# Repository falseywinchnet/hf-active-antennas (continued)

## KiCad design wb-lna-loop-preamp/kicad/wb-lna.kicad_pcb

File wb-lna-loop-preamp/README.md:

# WB-LNA: HF loop preamplifier

*Concept render: AI-generated (ChatGPT image generation) from the KiCad renders and the enclosure dimensions, with a ruler for scale. It shows the intended build; it is **not** a photograph of a built unit.*

WB-LNA is a single-ended HF (30 kHz – 30 MHz) low-noise amplifier with a high-impedance input. It suits a receiving loop or any other high-Z HF source.
- **Circuit:** 4× LSBF862 common source → 4× NSVF4009 common emitter with shunt-series feedback. The current is reused between the two stages.
- **Output:** a 3 dB π pad into 50 Ω SMA.
- **Power:** +12 V at 42 mA, from **either** the DC jack **or** phantom feed up the RF OUT coax.

## Performance
Simulated on the final board's layout-parasitic model, with a 50 Ω source and load at +12 V.

| | 1 MHz | 7 MHz | 14 MHz | 30 MHz |
|---|---|---|---|---|
| Gain | 24.0 dB | 24.0 dB | 24.0 dB | 23.2 dB |
| Noise figure | 0.80 dB | 0.81 dB | 0.87 dB | 1.14 dB |
| Noise temperature | 59 K | 60 K | 65 K | 87 K |
| Input return loss | 0.2 dB | 0.2 dB | 0.4 dB | 1.5 dB (high-Z input by design) |
| Output return loss | 52 dB | 46 dB | 37 dB | 24 dB |

**Linearity:**
- **Output P1dB:** +10.5 dBm (input −12.6 dBm).
- **OIP3 / IIP3** (−30 dBm/tone, 50 kHz spacing): +30.6 / +6.6 dBm at 7 MHz; +31.3 / +7.9 dBm at 28 MHz.
- **OIP2 / IIP2:** +36.3 / +12.3 dBm.
- **SFDR3 at 7 MHz:** 102 dB in 500 Hz.

**Low end:** flat to about 30 kHz; −3 dB at about 10 kHz.

**Stability:**
- **Tolerance corners:** 256 corners are all stable. They cover choke C and L, bead fits, trace and ground inductance, and gate-to-collector coupling.
- **Loop sources:** against any copper-wire loop into a receiver with |Γ| ≤ 1/3, the worst loop factor is 0.848.
- **Above 88 MHz:** μ ≥ 1.11 and μ′ ≥ 1.06.
- **Kicks:** node and differential kicks decay by ≥ 55 dB within 200 ns.

## How it works
- **Input:** the four LSBF862s run in parallel in common source.
  - Each has its own 100 nH‖60 Ω gate bead, with 100 kΩ gate bias and a BAV99 gate clamp.
  - The sources self-bias through R4/C4.
  - Paralleling four devices cuts en by about 2× against one device. Their combined input capacitance is the price; a loop's own reactance swamps it.
- **Drain:** loaded by 100 Ω AC, fed through a 1 mH choke.
- **Stage 2:** four onsemi NSVF4009 RF BJTs in common emitter.
  - R6/C8 provide shunt-series feedback and R7 the DC bias.
  - Each device has 22 Ω base and 10 Ω collector stoppers and 56 Ω emitter ballast.
- **Current reuse:** the JFET source bus is shared with the BJT collectors through L3, so the whole amplifier draws about 42 mA.
- **Output:** R8/C10 damp VHF, a 3 dB π pad (R40–R42) sets a clean 50 Ω match, and C13 blocks DC.
- **Protection:** a GDT (0.6 pF) plus 3× SP4022 on RF IN to the rear ground post, then VHF damping (L1‖R2).

**Power entry:** the two feeds are diode-ORed (D1/D8). The jack can never put DC on the receiver input, and the coax feed never appears on the jack.
- **Jack:** through a Würth 744222 common-mode choke. Its sleeve reaches board ground only through the choke winding.
- **Coax phantom feed:** L14 100 µH with 1 kΩ across it → L8 1 mH → a bead → 1 µF.
  - The 1 kΩ across L14 kills a series resonance between the two chokes. Without it, S22 has a −10 dB dip near 4 MHz.
- **Shared chain after the OR:** a PTC, a 15 V TVS, a 100 µH / 1 µF LC, then 22 Ω / 220 µF.
- **Differential rejection:** RF on the 12 V lead is rejected by ≥ 101 dB at 0.5–30 MHz, referred to the RF input.
- **Bias-T:** not supplied. Any bias-T rated ≥ 12 V / 100 mA with ≥ 1 kΩ choke impedance across 0.5–30 MHz will do.

## Plots

| plot | what |
|---|---|
| [`1_sparams_stability.png`](plots/1_sparams_stability.png) | S-parameters and μ/μ′ to 3 GHz |
| [`2_hf_gain_nf_match.png`](plots/2_hf_gain_nf_match.png) | HF gain, NF and match |
| [`3_transient_7MHz.png`](plots/3_transient_7MHz.png) | 7 MHz compression and collector swing |
| [`4_feedback_oscillation.png`](plots/4_feedback_oscillation.png) | output→input coupling test: ≤ 3.3 pF is stable, ≥ 10 pF oscillates |
| [`5_longrun_60s.png`](plots/5_longrun_60s.png) | 60 s runs, including power-up from the jack and from the coax |
| [`6_gain_nf_final.png`](plots/6_gain_nf_final.png) | gain and NF, final board |
| [`7_power_entry_chokes.png`](plots/7_power_entry_chokes.png) | power entry and choke impedances |

Plots 1–3, 6 and 7 use the layout-parasitic model. Plots 4 and 5 use the schematic without layout parasitics, because the layout model is too stiff for the long transients.

## LTspice model

`ltspice/wb-lna.asc` is the hand-laid schematic of the final circuit, with every board part. Keep `lsbf862-ltspice.lib`, `nsvf4009sg4-ltspice.lib` and `lna-parts.lib` next to it.
- **Test fixture:** V1 (AC 2) behind RS 50 Ω into RL 50 Ω, so `V(OUT)` is the transducer gain directly. The fixture is for simulation only.
- **Default analysis:** `.noise V(OUT) V1`, which reports NF re 50 Ω. Swap it for `.ac` to get gain.
- **Model fidelity:** checked against the design's reference netlist, it gives identical NF and gain within 0.1 dB.
- **Board copper:** the schematic carries no layout parasitics. The board's parasitic model, which the plots use, adds them.

## Board and ordering

**Board:**
- 92.4 × 42.4 mm, 2 layers, 1.6 mm FR-4, 1 oz copper, solid GND pours on both layers.
- **Enclosure:** Hammond 1591A (= RS PRO 153-3681, 100 × 50 × 25 mm).
- **Mounting:** 4 × M3 holes at 86.2 × 36.2 mm centres.
- **Connectors:** SMA RF IN on the front edge; SMA RF OUT and the 12 V jack on the rear edge.

**JLCPCB fabrication:** upload `jlcpcb/wb-lna_gerbers_drill.zip`.
- 2 layers, 1.6 mm, 1 oz;
- min track/clearance 0.2 mm, smallest via 0.6 / 0.3 mm.

**JLCPCB assembly:** `jlcpcb/BOM_JLCPCB.csv` and `jlcpcb/CPL_JLCPCB.csv`, on the same origin as the gerbers.
- **LCSC numbers:** left blank. Let JLC match parts by MPN or spec.
- **LSBF862:** buy from Linear Integrated Systems.
- **Candidate parts:** rows marked `candidate - verify before ordering` were not checked against a datasheet. They are the Murata beads L4/L5/L9/L10–L13, the R9 PTC and the C1 electrolytic.
- **Hand-solder:** the edge-mount SMAs X1/X2 and the THT jack X3.
- **Rotation:** check every part's rotation in the placement preview. This matters most for SOT-23, the SMA/SMB diodes, the electrolytic and the WE-SL2 choke; pin 1 of the choke is the dotted corner.

**Lands:**
- **J1–J4:** a custom SOT-23 land with shortened inner heels, so the source bus can run under the bodies.
- **Q1–Q4:** onsemi's SC-82FL land.
- **The 2220 chokes:** the B82442T datasheet pattern.

**Install:** the coax shield still carries common-mode RF. Fit a clip-on 31-mix ferrite on the coax at the amplifier.

## Files

| path | what |
|---|---|
| `ltspice/` | `wb-lna.asc` and its three model libraries |
| `images/` | concept render in the enclosure (AI-generated); 3D renders (iso, top), top copper coloured by net, schematic (PNG, SVG) |
| `plots/` | LTspice results (table above) |
| `jlcpcb/` | the gerber + drill zip (Protel extensions, Excellon mm, PTH/NPTH separate, job file), the unzipped files, `BOM_JLCPCB.csv`, `CPL_JLCPCB.csv` |
| `BOM.csv` | the full BOM: qty, designators, value, description, manufacturer, MPN, footprint, status |
| `kicad/` | `wb-lna.kicad_pcb`, the project, the custom footprint library `wblna.pretty`, the DRC report |
| `wb-lna.step` | 3D board model. The L6 body is a scaled stand-in. |

**Not claimed:** any surge/ESD rating or measured performance. All figures are simulation.

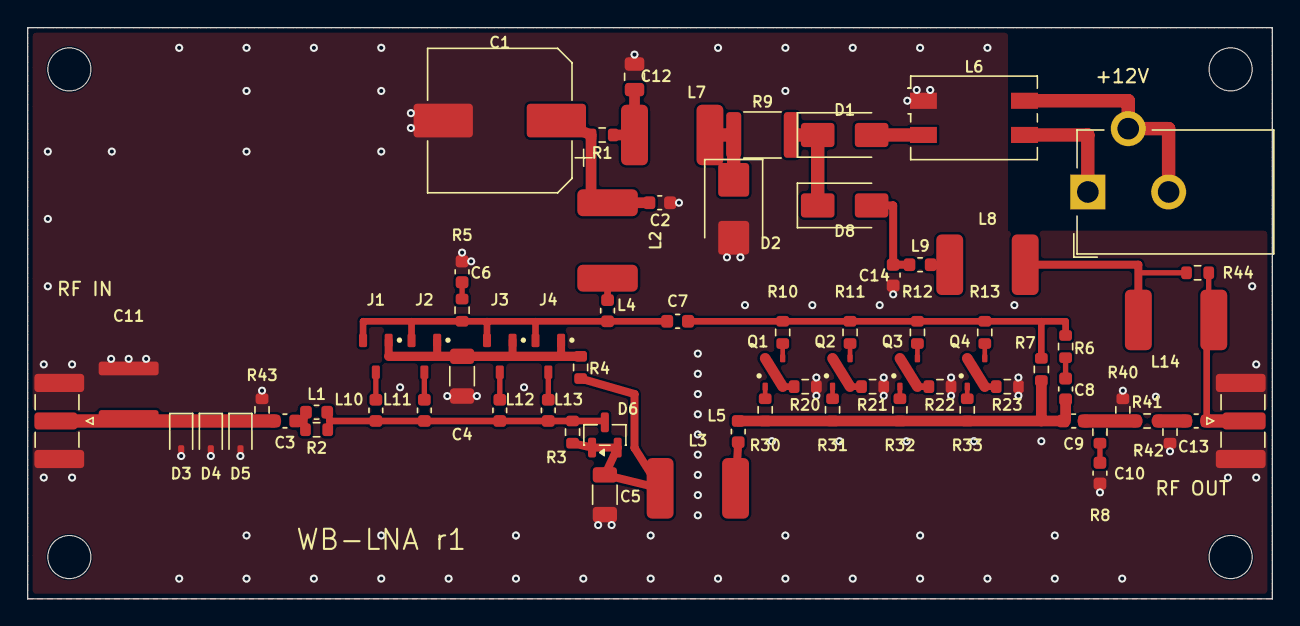
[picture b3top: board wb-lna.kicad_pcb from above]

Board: 2 copper layers, 92.4 x 42.4 mm, 76 parts (0 on the bottom side), 43 nets.

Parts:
C1: 220u; CP_Elec_10x10.5
C2: C2; C_0603_1608Metric
C3: C3; C_0603_1608Metric
C4: C4; C_1206_3216Metric
C5: C5; C_1206_3216Metric
C6: C6; C_0603_1608Metric
C7: C7; C_0603_1608Metric
C8: C8; C_0603_1608Metric
C9: C9; C_0603_1608Metric
C10: C10; C_0603_1608Metric
C11: GDT25-09-S1; GDT25_S1
C12: 1u; C_0805_2012Metric
C13, C14: 1u; C_0603_1608Metric
D1, D8: SS14; D_SMA
D2: SMBJ15A; D_SMB
D3, D4, D5: SP4022; D_SOD-323
D6: BAV99; SOT-23
H1, H2, H3, H4: M3; MountingHole_3.2mm_M3
J1, J2, J3, J4: LSBF862; SOT-23_WB
L1: 82nH; L_0603_1608Metric
L2, L3, L8: 1mH; L_2220_SIMID
L4, L5, L9: 600R@100M; L_0603_1608Metric
L6: 744222; L_CommonMode_Wuerth_WE-SL2
L7, L14: 100uH; L_2220_SIMID
L10, L11, L12, L13: bead; L_0603_1608Metric
Q1, Q2, Q3, Q4: NSVF4009SG4; SC-82FL_MCPH4
R1: R1; R_0603_1608Metric
R2: 47; R_0603_1608Metric
R3: R3; R_0603_1608Metric
R4: R4; R_0603_1608Metric
R5: R5; R_0603_1608Metric
R6: R6; R_0603_1608Metric
R7: R7; R_0603_1608Metric
R8: R8; R_0603_1608Metric
R9: PTC; R_1812_4532Metric
R10: R10; R_0603_1608Metric
R11: R11; R_0603_1608Metric
R12: R12; R_0603_1608Metric
R13: R13; R_0603_1608Metric
R20: R20; R_0603_1608Metric
R21: R21; R_0603_1608Metric
R22: R22; R_0603_1608Metric
R23: R23; R_0603_1608Metric
R30: R30; R_0603_1608Metric
R31: R31; R_0603_1608Metric
R32: R32; R_0603_1608Metric
R33: R33; R_0603_1608Metric
R40, R42: 294; R_0603_1608Metric
R41: 17.8; R_0603_1608Metric
R43: 4.7k; R_0603_1608Metric
R44: 1k; R_0603_1608Metric
X1: SMA RF IN; SMA_Samtec_SMA-J-P-H-ST-EM1_EdgeMount
X2: SMA RF OUT; SMA_Samtec_SMA-J-P-H-ST-EM1_EdgeMount
X3: 12V; BarrelJack_CUI_PJ-102AH_Horizontal

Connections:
B0: Q1.3, R10.2
B1: Q2.3, R11.2
B2: Q3.3, R12.2
B3: Q4.3, R13.2
BASE: C7.2, R6.2, R7.2, R10.1, R11.1, R12.1, R13.1
C0: Q1.1, R30.1
C1: Q2.1, R31.1
C2: Q3.1, R32.1
C3: Q4.1, R33.1
CBL_GND: L6.4, X3.2, X3.3
COLL: C8.1, C9.1, L5.2, R7.1, R30.2, R31.2, R32.2, R33.2
DQ: C6.1, R5.2
E0: Q1.2, Q1.4, R20.1
E1: Q2.2, Q2.4, R21.1
E2: Q3.2, Q3.4, R22.1
E3: Q4.2, Q4.4, R23.1
FB2: C8.2, R6.1
G0: J1.3, L10.2
G1: J2.3, L11.2
G2: J3.3, L12.2
G3: J4.3, L13.2
GATE: D6.3, L1.2, L10.1, L11.1, L12.1, L13.1, R2.2, R3.1
GATE_IN: C3.2, L1.1, R2.1
GND: C1.2, C2.2, C4.2, C5.2, C6.2, C10.2, C11.2, C12.2, C14.2, D2.2, D3.2, D4.2, D5.2, L6.1, R20.2, R21.2, R22.2, R23.2, R40.2, R42.2, R43.2, X1.2, X2.2
JFET_D: C7.1, J1.2, J2.2, J3.2, J4.2, L4.2, R5.1
JFET_S: C4.1, J1.1, J2.1, J3.1, J4.1, R4.1
L2B: L2.2, L4.1
L3B: L3.2, L5.1
L8C: L8.1, L9.2
L8H: L8.2, L14.1, R44.1
OUT_DAMP: C10.1, R8.2
PAD_OUT: C13.1, R41.2, R42.1
RF_AMP: C9.2, R8.1, R40.1, R41.1
RF_IN: C3.1, C11.1, D3.1, D4.1, D5.1, R43.1, X1.1
RF_OUT: C13.2, L14.2, R44.2, X2.1
VCF: C14.1, D8.2, L9.1
VDD: C1.1, C2.1, L2.1, R1.2
VIN_12V: L6.3, X3.1
VJ: D1.2, L6.2
VOR: D1.1, D8.1, R9.1
VP: D2.1, L7.2, R9.2
VQ: C12.1, L7.1, R1.1
VSRC: C5.1, D6.1, D6.2, L3.1, R3.2, R4.2

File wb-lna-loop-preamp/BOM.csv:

Qty,Designators,Value,Description,Manufacturer,MPN,Footprint,Status
1,C1,220uF 25V,"Aluminium electrolytic, SMD 10x10.5 mm can",Panasonic,EEE-FC1E221P,CP_Elec_10x10.5,candidate - verify before ordering
1,C2,100nF 50V,MLCC X7R 0603,,,C_0603_1608Metric,generic - any vendor to spec
1,C3,1uF 50V,MLCC X7R 0603 (input DC block),,,C_0603_1608Metric,generic - any vendor to spec
1,C4,47uF 10V,MLCC X5R 1206 (JFET source bypass),,,C_1206_3216Metric,generic - any vendor to spec
1,C5,47uF 10V,MLCC X5R 1206 (VSRC bypass),,,C_1206_3216Metric,generic - any vendor to spec
4,C6 C7 C8 C9,1uF 25V,MLCC X7R 0603,,,C_0603_1608Metric,generic - any vendor to spec
1,C10,15pF 50V,MLCC C0G 0603,,,C_0603_1608Metric,generic - any vendor to spec
1,C11,GDT 90V,"Gas discharge tube, 2-electrode SMD",Bourns,GDT25-09-S1-RP,GDT25_S1,verified against datasheet
1,C12,1uF 50V,MLCC X7R 0805 (DM supply filter),,,C_0805_2012Metric,generic - any vendor to spec
1,C13,1uF 50V,MLCC X7R 0603 (output DC block: the coax may carry +12V),,,C_0603_1608Metric,generic - any vendor to spec
1,C14,1uF 50V,MLCC X7R 0603 (L8 cold-end bypass; 1u puts the L8/C14 notch at ~5 kHz),,,C_0603_1608Metric,generic - any vendor to spec
1,D1,SS14,"Schottky 40V 1A, SMA (jack feed: reverse polarity + OR)",,SS14,D_SMA,generic - any vendor to spec
1,D2,SMBJ15A,"TVS 15V unidirectional, SMB",,SMBJ15A,D_SMB,generic - any vendor to spec
3,D3 D4 D5,SP4022,"TVS array, bidirectional, SOD-323 (RF input)",Littelfuse,SP4022-01FTG-C,D_SOD-323,verified against datasheet
1,D6,BAV99,"Dual switching diode, SOT-23 (gate clamp)",,BAV99,SOT-23,generic - any vendor to spec
1,D8,SS14,"Schottky 40V 1A, SMA (coax feed: OR diode)",,SS14,D_SMA,generic - any vendor to spec
4,J1 J2 J3 J4,LSBF862,"N-channel JFET, SOT-23 (1=S 2=D 3=G)",Linear Integrated Systems,LSBF862 SOT-23,SOT-23_WB,verified against datasheet
1,L1,82nH,"Ceramic-core wirewound 0603, Q>=34@250MHz, SRF>=1.7GHz",Coilcraft,0603CS-82NXJRW,L_0603_1608Metric,verified against datasheet
2,L2 L3,1mH,"SMD choke SIMID 2220-T, Itemp 150mA, Rmax 9.5ohm, SRF>=1.8MHz (replaces obsolete B82442H1105K000)",TDK,B82442T1105K000,L_2220_SIMID,verified against datasheet
2,L4 L5,600R@100MHz,"Ferrite bead 0603, >=200mA (choke hot-end damping)",Murata,BLM18KG601SN1D,L_0603_1608Metric,candidate - verify before ordering
1,L6,744222,"Common-mode choke WE-SL2 2x1000uH, 800mA, 0.207ohm; CM |Z| >=1k 0.12-50MHz (12V jack entry)",Wurth Elektronik,744222,L_CommonMode_Wuerth_WE-SL2,verified against datasheet
1,L7,100uH,"SMD choke SIMID 2220-T, Itemp 510mA, Rmax 0.99ohm, SRF>=6.1MHz (DM supply filter)",TDK,B82442T1104K000,L_2220_SIMID,verified against datasheet
1,L8,1mH,"SMD choke SIMID 2220-T, coax phantom-feed choke, Itemp 150mA, Rmax 9.5ohm, SRF>=1.8MHz",TDK,B82442T1105K000,L_2220_SIMID,verified against datasheet
1,L9,600R@100MHz,"Ferrite bead 0603, >=200mA (L8 cold-end UHF damping)",Murata,BLM18KG601SN1D,L_0603_1608Metric,candidate - verify before ordering
4,L10 L11 L12 L13,60R@100MHz,Ferrite bead 0603 (gate stopper),Murata,BLM18BB600SN1D,L_0603_1608Metric,candidate - verify before ordering
1,L14,100uH,"SMD choke SIMID 2220-T, coax-feed hot section in series with L8, Itemp 510mA, Rmax 0.99ohm, SRF>=6.1MHz",TDK,B82442T1104K000,L_2220_SIMID,verified against datasheet
4,Q1 Q2 Q3 Q4,NSVF4009SG4,"RF NPN 25GHz, SC-82FL/MCPH4 (1=C 2,4=E 3=B)",onsemi,NSVF4009SG4T1G,SC-82FL_MCPH4,verified against datasheet
5,R1 R10 R11 R12 R13,22,Resistor 0603 1% thick film,,,R_0603_1608Metric,generic - any vendor to spec
2,R2 R8,47,Resistor 0603 1% thick film,,,R_0603_1608Metric,generic - any vendor to spec
1,R3,100k,Resistor 0603 1% thick film,,,R_0603_1608Metric,generic - any vendor to spec
1,R4,3.3,Resistor 0603 1% thick film,,,R_0603_1608Metric,generic - any vendor to spec
1,R5,100,Resistor 0603 1% thick film,,,R_0603_1608Metric,generic - any vendor to spec
1,R6,270,Resistor 0603 1% thick film,,,R_0603_1608Metric,generic - any vendor to spec
1,R7,3.0k,Resistor 0603 1% thick film,,,R_0603_1608Metric,generic - any vendor to spec
1,R9,PTC 0.1A hold,"Resettable fuse 1812, Ihold ~100mA, >=16V",Bourns,MF-MSMF010-2,R_1812_4532Metric,candidate - verify before ordering
4,R20 R21 R22 R23,56,Resistor 0603 1% thick film,,,R_0603_1608Metric,generic - any vendor to spec
4,R30 R31 R32 R33,10,Resistor 0603 1% thick film,,,R_0603_1608Metric,generic - any vendor to spec
2,R40 R42,294,Resistor 0603 1% thick film,,,R_0603_1608Metric,generic - any vendor to spec
1,R41,17.8,Resistor 0603 1% thick film,,,R_0603_1608Metric,generic - any vendor to spec
1,R43,4.7k,Resistor 0603 1% thick film,,,R_0603_1608Metric,generic - any vendor to spec
1,R44,1k,Resistor 0603 1% thick film,,,R_0603_1608Metric,generic - any vendor to spec
1,X1,SMA RF IN,"SMA jack, edge mount, 1.6 mm board",Samtec,SMA-J-P-H-ST-EM1,SMA_Samtec_SMA-J-P-H-ST-EM1_EdgeMount,footprint from KiCad library - confirm part
1,X2,SMA RF OUT,"SMA jack, edge mount, 1.6 mm board",Samtec,SMA-J-P-H-ST-EM1,SMA_Samtec_SMA-J-P-H-ST-EM1_EdgeMount,footprint from KiCad library - confirm part
1,X3,12V DC jack,"2.1 mm DC barrel jack, through hole",CUI,PJ-102AH,BarrelJack_CUI_PJ-102AH_Horizontal,footprint from KiCad library - confirm part
